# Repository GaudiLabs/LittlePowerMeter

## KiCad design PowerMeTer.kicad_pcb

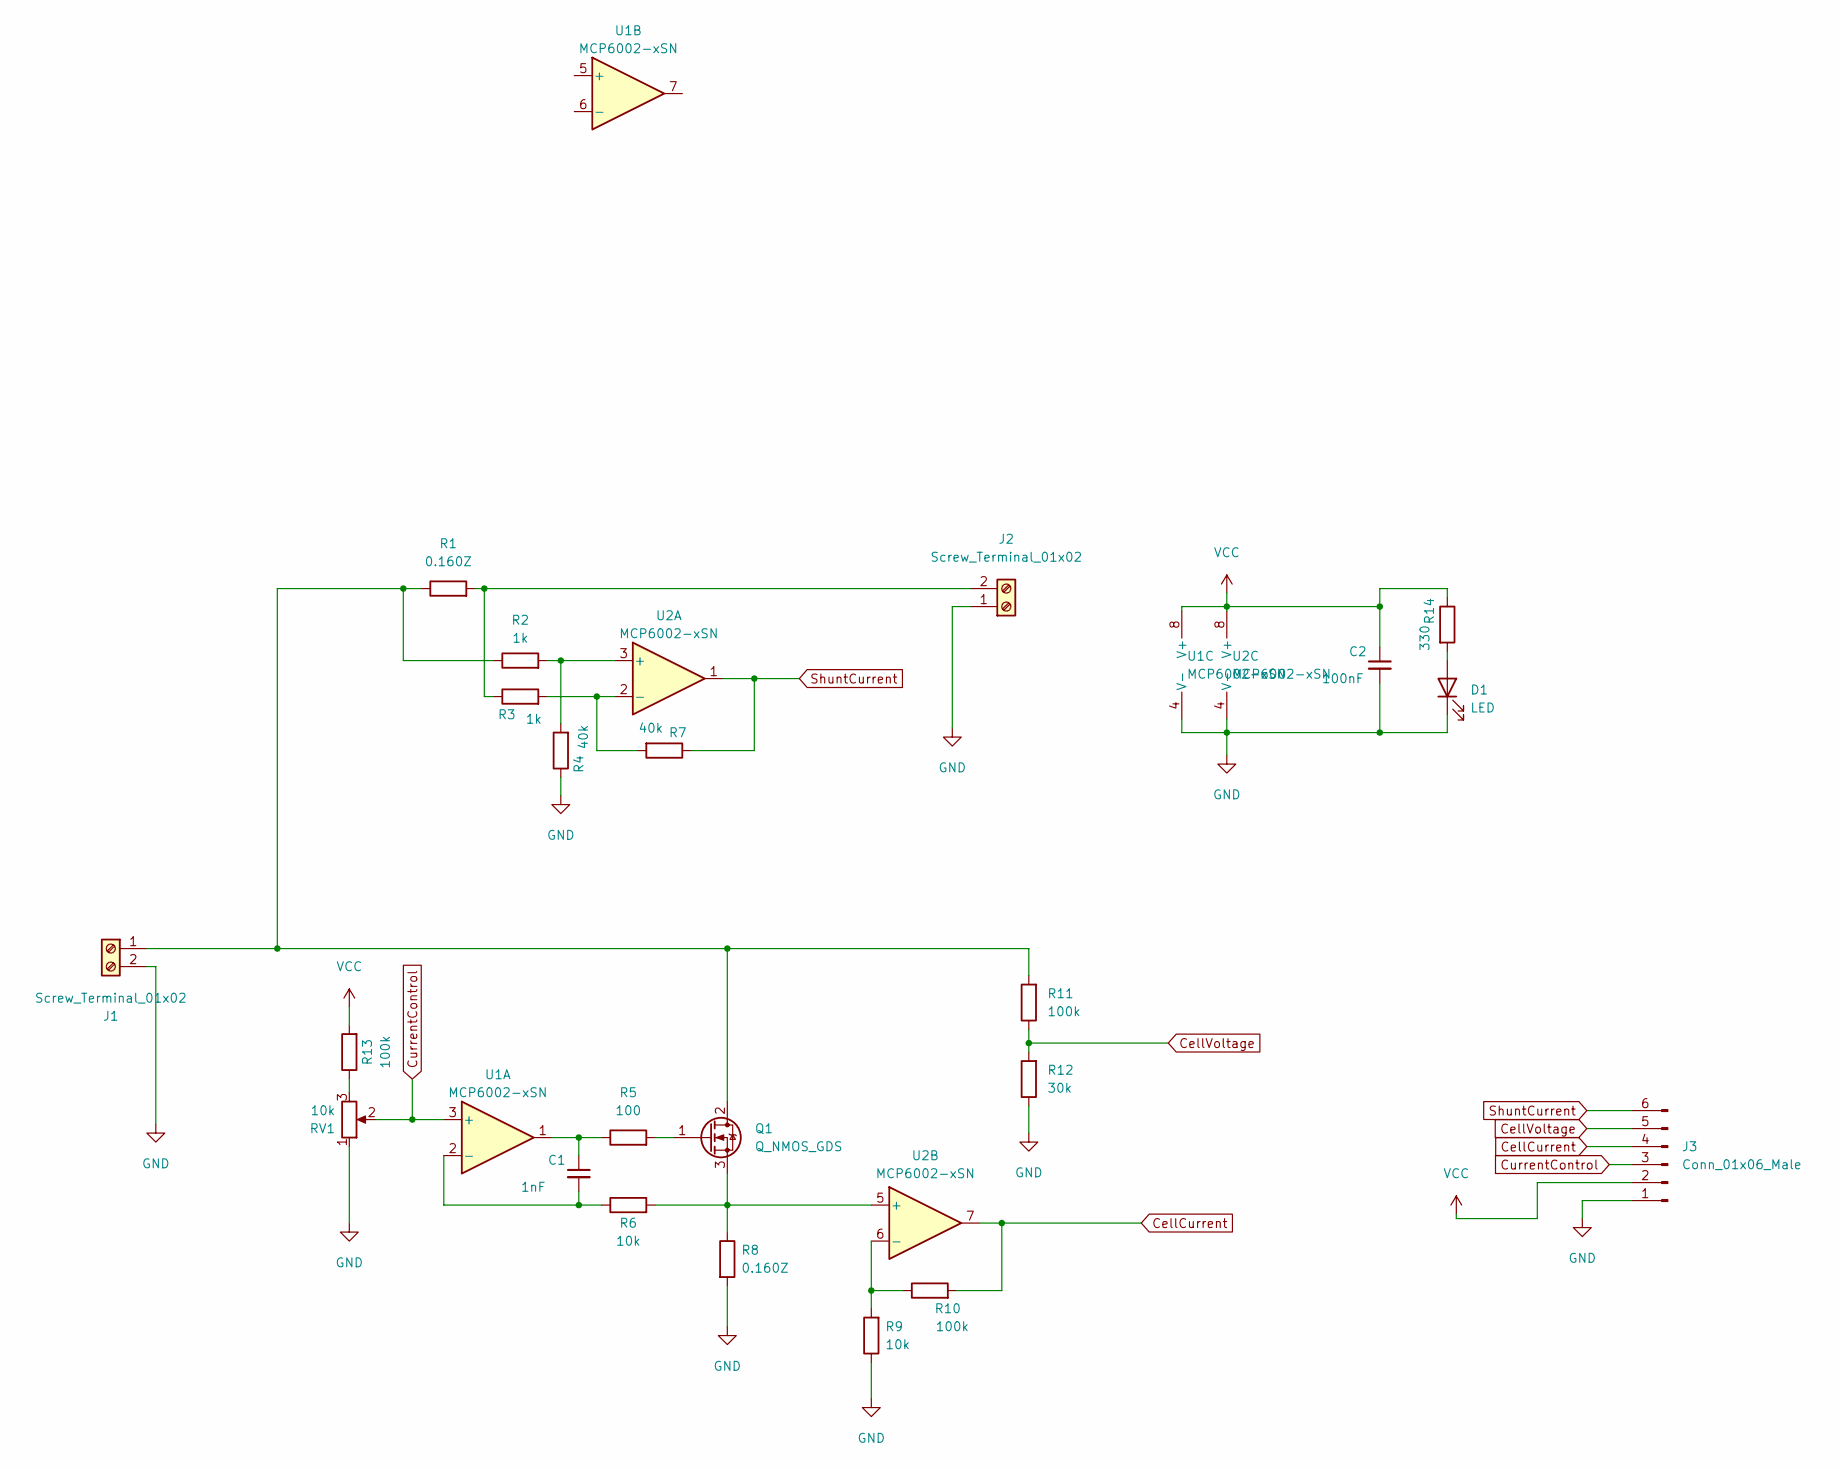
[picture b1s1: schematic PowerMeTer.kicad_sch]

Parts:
C1: 1nF; C_0805_2012Metric
C2: 100nF; C_0805_2012Metric
D1: LED; LED_0805_2012Metric
J1, J2: Screw_Terminal_01x02; TerminalBlock_RND_205-00012_1x02_P5.00mm_Horizontal
J3: Conn_01x06_Male; Molex_KK-254_AE-6410-06A_1x06_P2.54mm_Vertical
Q1: Q_NMOS_GDS; TO-252-2
R1, R8: 0.160Z; R_0805_2012Metric
R2, R3: 1k; R_0805_2012Metric
R4, R7: 40k; R_0805_2012Metric
R5: 100; R_0805_2012Metric
R6, R9: 10k; R_0805_2012Metric
R10, R11, R13: 100k; R_0805_2012Metric
R12: 30k; R_0805_2012Metric
R14: 330; R_0805_2012Metric
RV1: 10k; Alps_RK09K_Vertical
U1, U2: MCP6002-xSN; SOIC-8_3.9x4.9mm_P1.27mm

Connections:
CellCurrent: J3.4, R10.2, U2.7
CellVoltage: J3.5, R11.1, R12.2
CurrentControl: J3.3, RV1.2, U1.3 (+)
GND: C2.2, D1.1 (K), J1.2, J2.1, J3.1, R4.1, R8.2, R9.1, R12.1, RV1.1, U1.4 (V-), U2.4 (V-)
unnamed: C1.1, R5.1, U1.1
unnamed: C1.2, R6.1, U1.2 (-)
unnamed: D1.2 (A), R14.2
unnamed: J1.1, Q1.2 (D), R1.1, R2.1, R11.2
unnamed: J2.2, R1.2, R3.1
unnamed: Q1.1 (G), R5.2
unnamed: Q1.3 (S), R6.2, R8.1, U2.5 (+)
unnamed: R2.2, R4.2, U2.3 (+)
unnamed: R3.2, R7.2, U2.2 (-)
unnamed: R9.2, R10.1, U2.6 (-)
unnamed: R13.1, RV1.3
ShuntCurrent: J3.6, R7.1, U2.1
VCC: C2.1, J3.2, R13.2, R14.1, U1.8 (V+), U2.8 (V+)

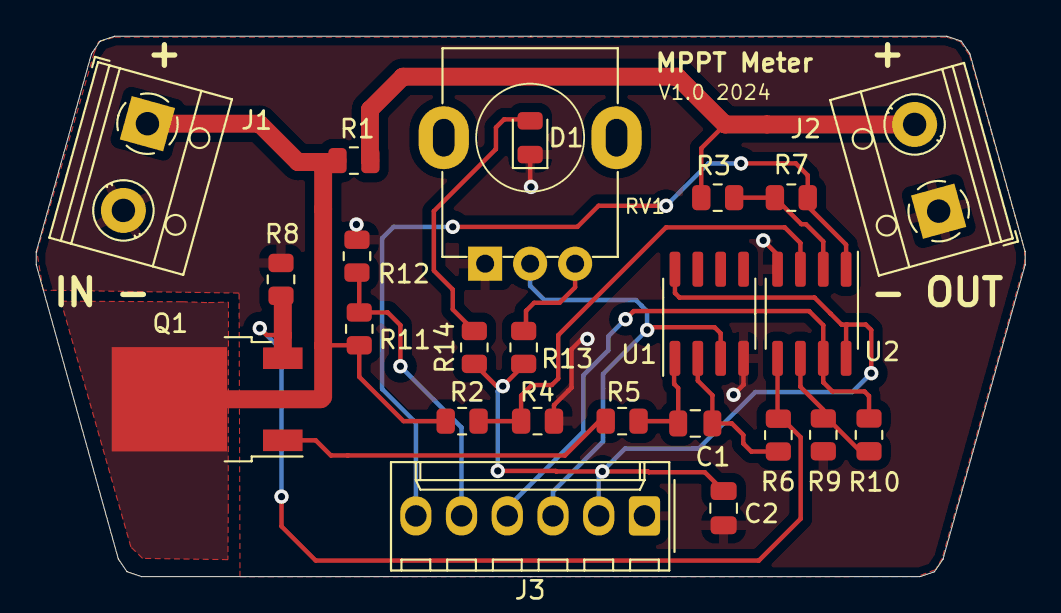
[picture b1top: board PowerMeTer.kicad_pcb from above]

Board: 2 copper layers, 54.9 x 30.0 mm, 24 parts (0 on the bottom side), 17 nets.

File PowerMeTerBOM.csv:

"Id";"Designator";"Package";"Quantity";"Designation";"Supplier and ref";
1;"J2,J1";"TerminalBlock_RND_205-00012_1x02_P5.00mm_Horizontal";2;"Screw_Terminal_01x02";;;
2;"R7,R4";"R_0805_2012Metric";2;"40k";;;
3;"J3";"Molex_KK-254_AE-6410-06A_1x06_P2.54mm_Vertical";1;"Conn_01x06_Male";;;
4;"R2,R3";"R_0805_2012Metric";2;"1k";;;
5;"U1,U2";"SOIC-8_3.9x4.9mm_P1.27mm";2;"MCP6002-xSN";;;
6;"R1,R8";"R_0805_2012Metric";2;"0.160Z";;;
7;"R5";"R_0805_2012Metric";1;"100";;;
8;"Q1";"TO-252-2";1;"Q_NMOS_GDS";;;
9;"D1";"LED_0805_2012Metric";1;"LED";;;
10;"C2";"C_0805_2012Metric";1;"100nF";;;
11;"R13,R11,R10";"R_0805_2012Metric";3;"100k";;;
12;"R6,R9";"R_0805_2012Metric";2;"10k";;;
13;"R14";"R_0805_2012Metric";1;"330";;;
14;"C1";"C_0805_2012Metric";1;"1nF";;;
15;"RV1";"Alps_RK09K_Vertical";1;"10k";;;
16;"R12";"R_0805_2012Metric";1;"30k";;;

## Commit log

2025-01-20 First Release
